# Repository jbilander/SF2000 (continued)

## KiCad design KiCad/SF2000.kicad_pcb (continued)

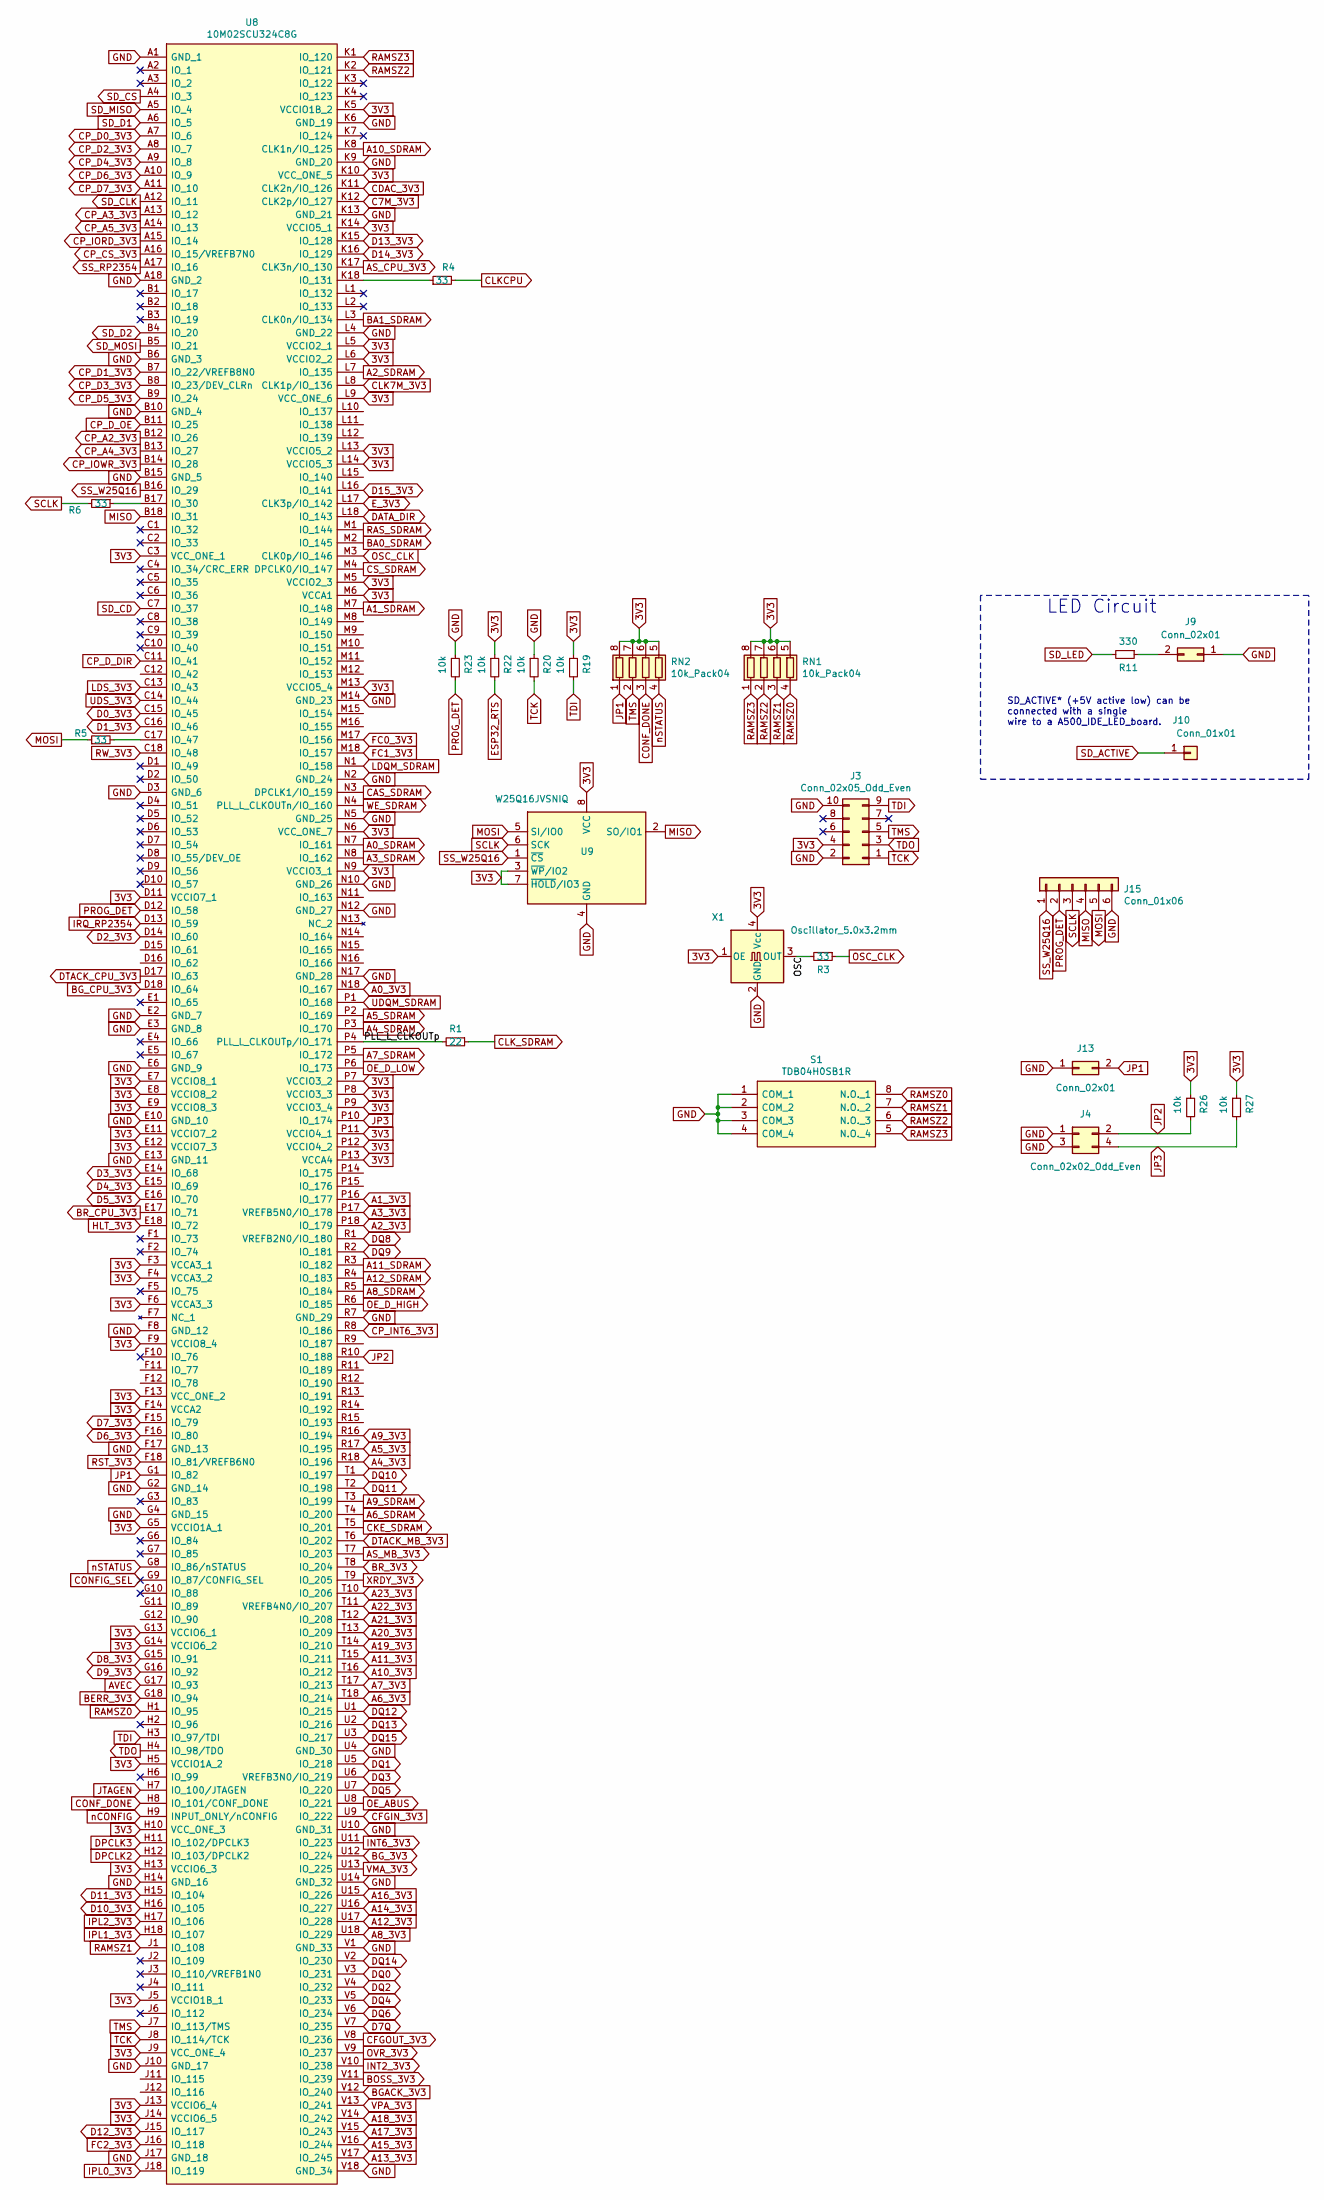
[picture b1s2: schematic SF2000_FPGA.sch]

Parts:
J3: Conn_02x05_Odd_Even; PinHeader_2x05_P2.54mm_Vertical
J4: Conn_02x02_Odd_Even; PinHeader_2x02_P2.54mm_Vertical
J9, J13: Conn_02x01; PinHeader_2x01_P2.54mm_Vertical
J10: Conn_01x01; PinHeader_1x01_P2.54mm_Horizontal
J15: Conn_01x06; PinHeader_1x06_P2.54mm_Vertical
R1: 22; R_0603_1608Metric_Pad0.98x0.95mm_HandSolder
R3, R4, R5, R6: 33; R_0603_1608Metric_Pad0.98x0.95mm_HandSolder
R11: 330; R_0603_1608Metric_Pad0.98x0.95mm_HandSolder
R19, R20, R22, R23, R26, R27: 10k; R_0603_1608Metric_Pad0.98x0.95mm_HandSolder
RN1, RN2: 10k_Pack04; RESCAF80P320X160X60-8N
S1: TDB04H0SB1R; TDB04H0SB1
U8: 10M02SCU324C8G; BGA-324_15.0x15.0mm_Layout18x18_P0.8mm_Ball0.5mm_Pad0.4mm_N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
U9: W25Q16JVSNIQ; SOIC-8_3.9x4.9mm_P1.27mm
X1: Oscillator_5.0x3.2mm; Oscillator_SMD_SeikoEpson_SG8002LB-4Pin_5.0x3.2mm

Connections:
3V3: J3.4, R19.1, R22.1, R26.1, R27.1, RN1.5 (R4.2), RN1.6 (R3.2), RN1.7 (R2.2), RN1.8 (R1.2), RN2.5 (R4.2), RN2.6 (R3.2), RN2.7 (R2.2), RN2.8 (R1.2), U8.C3 (VCC_ONE_1), U8.D11 (VCCIO7_1), U8.E7 (VCCIO8_1), U8.E8 (VCCIO8_2), U8.E9 (VCCIO8_3), U8.E11 (VCCIO7_2), U8.E12 (VCCIO7_3), U8.F3 (VCCA3_1), U8.F4 (VCCA3_2), U8.F6 (VCCA3_3), U8.F9 (VCCIO8_4), U8.F13 (VCC_ONE_2), U8.F14 (VCCA2), U8.G5 (VCCIO1A_1), U8.G13 (VCCIO6_1), U8.G14 (VCCIO6_2), U8.H5 (VCCIO1A_2), U8.H10 (VCC_ONE_3), U8.H13 (VCCIO6_3), U8.J5 (VCCIO1B_1), U8.J9 (VCC_ONE_4), U8.J13 (VCCIO6_4), U8.J14 (VCCIO6_5), U8.K5 (VCCIO1B_2), U8.K10 (VCC_ONE_5), U8.K14 (VCCIO5_1), U8.L5 (VCCIO2_1), U8.L6 (VCCIO2_2), U8.L9 (VCC_ONE_6), U8.L13 (VCCIO5_2), U8.L14 (VCCIO5_3), U8.M5 (VCCIO2_3), U8.M6 (VCCA1), U8.M13 (VCCIO5_4), U8.N6 (VCC_ONE_7), U8.N9 (VCCIO3_1), U8.P7 (VCCIO3_2), U8.P8 (VCCIO3_3), U8.P9 (VCCIO3_4), U8.P11 (VCCIO4_1), U8.P12 (VCCIO4_2), U8.P13 (VCCA4), U9.3 (~WP~/IO2), U9.7 (~HOLD~/IO3), U9.8 (VCC), X1.1 (OE), X1.4 (Vcc); also elsewhere on the board
/SF2000_FPGA/OSC: R3.2, X1.3 (OUT)
/SF2000_FPGA/PLL_L_CLKOUTp: R1.2, U8.P4 (PLL_L_CLKOUTp/IO_171)
A0_3V3: U8.N18 (IO_167); also elsewhere on the board
A0_SDRAM: U8.N7 (IO_161); also elsewhere on the board
A1_3V3: U8.P16 (IO_177); also elsewhere on the board
A1_SDRAM: U8.M7 (IO_148); also elsewhere on the board
A2_3V3: U8.P18 (IO_179); also elsewhere on the board
A2_SDRAM: U8.L7 (IO_135); also elsewhere on the board
A3_3V3: U8.P17 (VREFB5N0/IO_178); also elsewhere on the board
A3_SDRAM: U8.N8 (IO_162); also elsewhere on the board
A4_3V3: U8.R18 (IO_196); also elsewhere on the board
A4_SDRAM: U8.P3 (IO_170); also elsewhere on the board
A5_3V3: U8.R17 (IO_195); also elsewhere on the board
A5_SDRAM: U8.P2 (IO_169); also elsewhere on the board
A6_3V3: U8.T18 (IO_214); also elsewhere on the board
A6_SDRAM: U8.T4 (IO_200); also elsewhere on the board
A7_3V3: U8.T17 (IO_213); also elsewhere on the board
A7_SDRAM: U8.P5 (IO_172); also elsewhere on the board
A8_3V3: U8.U18 (IO_229); also elsewhere on the board
A8_SDRAM: U8.R5 (IO_184); also elsewhere on the board
A9_3V3: U8.R16 (IO_194); also elsewhere on the board
A9_SDRAM: U8.T3 (IO_199); also elsewhere on the board
A10_3V3: U8.T16 (IO_212); also elsewhere on the board
A10_SDRAM: U8.K8 (CLK1n/IO_125); also elsewhere on the board
A11_3V3: U8.T15 (IO_211); also elsewhere on the board
A11_SDRAM: U8.R3 (IO_182); also elsewhere on the board
A12_3V3: U8.U17 (IO_228); also elsewhere on the board
A12_SDRAM: U8.R4 (IO_183); also elsewhere on the board
A13_3V3: U8.V17 (IO_245); also elsewhere on the board
A14_3V3: U8.U16 (IO_227); also elsewhere on the board
A15_3V3: U8.V16 (IO_244); also elsewhere on the board
A16_3V3: U8.U15 (IO_226); also elsewhere on the board
A17_3V3: U8.V15 (IO_243); also elsewhere on the board
A18_3V3: U8.V14 (IO_242); also elsewhere on the board
A19_3V3: U8.T14 (IO_210); also elsewhere on the board
A20_3V3: U8.T13 (IO_209); also elsewhere on the board
A21_3V3: U8.T12 (IO_208); also elsewhere on the board
A22_3V3: U8.T11 (VREFB4N0/IO_207); also elsewhere on the board
A23_3V3: U8.T10 (IO_206); also elsewhere on the board
AS_CPU_3V3: U8.K17 (CLK3n/IO_130); also elsewhere on the board
AS_MB_3V3: U8.T7 (IO_203); also elsewhere on the board
AVEC: U8.G17 (IO_93); also elsewhere on the board
BA0_SDRAM: U8.M2 (IO_145); also elsewhere on the board
BA1_SDRAM: U8.L3 (CLK0n/IO_134); also elsewhere on the board
BERR_3V3: U8.G18 (IO_94); also elsewhere on the board
BGACK_3V3: U8.V12 (IO_240); also elsewhere on the board
BG_3V3: U8.U12 (IO_224); also elsewhere on the board
BG_CPU_3V3: U8.D18 (IO_64); also elsewhere on the board
BOSS_3V3: U8.V11 (IO_239); also elsewhere on the board
BR_3V3: U8.T8 (IO_204); also elsewhere on the board
BR_CPU_3V3: U8.E17 (IO_71); also elsewhere on the board
C7M_3V3: U8.K12 (CLK2p/IO_127); also elsewhere on the board
CAS_SDRAM: U8.N3 (DPCLK1/IO_159); also elsewhere on the board
CDAC_3V3: U8.K11 (CLK2n/IO_126); also elsewhere on the board
CFGIN_3V3: U8.U9 (IO_222); also elsewhere on the board
CFGOUT_3V3: U8.V8 (IO_236); also elsewhere on the board
CKE_SDRAM: U8.T5 (IO_201); also elsewhere on the board
CLK7M_3V3: U8.L8 (CLK1p/IO_136); also elsewhere on the board
CLKCPU: R4.2; also elsewhere on the board
CLK_SDRAM: R1.1; also elsewhere on the board
CONFIG_SEL: U8.G9 (IO_87/CONFIG_SEL)
CONF_DONE: RN2.3 (R3.1), U8.H8 (IO_101/CONF_DONE)
CP_A2_3V3: U8.B12 (IO_26); also elsewhere on the board
CP_A3_3V3: U8.A13 (IO_12); also elsewhere on the board
CP_A4_3V3: U8.B13 (IO_27); also elsewhere on the board
CP_A5_3V3: U8.A14 (IO_13); also elsewhere on the board
CP_CS_3V3: U8.A16 (IO_15/VREFB7N0); also elsewhere on the board
CP_D0_3V3: U8.A7 (IO_6); also elsewhere on the board
CP_D1_3V3: U8.B7 (IO_22/VREFB8N0); also elsewhere on the board
CP_D2_3V3: U8.A8 (IO_7); also elsewhere on the board
CP_D3_3V3: U8.B8 (IO_23/DEV_CLRn); also elsewhere on the board
CP_D4_3V3: U8.A9 (IO_8); also elsewhere on the board
CP_D5_3V3: U8.B9 (IO_24); also elsewhere on the board
CP_D6_3V3: U8.A10 (IO_9); also elsewhere on the board
CP_D7_3V3: U8.A11 (IO_10); also elsewhere on the board
CP_D_DIR: U8.C11 (IO_41); also elsewhere on the board
CP_D_OE: U8.B11 (IO_25); also elsewhere on the board
CP_INT6_3V3: U8.R8 (IO_186); also elsewhere on the board
CP_IORD_3V3: U8.A15 (IO_14); also elsewhere on the board
CP_IOWR_3V3: U8.B14 (IO_28); also elsewhere on the board
CS_SDRAM: U8.M4 (DPCLK0/IO_147); also elsewhere on the board
D0_3V3: U8.C15 (IO_45); also elsewhere on the board
D1_3V3: U8.C16 (IO_46); also elsewhere on the board
D2_3V3: U8.D14 (IO_60); also elsewhere on the board
D3_3V3: U8.E14 (IO_68); also elsewhere on the board
D4_3V3: U8.E15 (IO_69); also elsewhere on the board
D5_3V3: U8.E16 (IO_70); also elsewhere on the board
D6_3V3: U8.F16 (IO_80); also elsewhere on the board
D7Q: U8.V7 (IO_235); also elsewhere on the board
D7_3V3: U8.F15 (IO_79); also elsewhere on the board
D8_3V3: U8.G15 (IO_91); also elsewhere on the board
D9_3V3: U8.G16 (IO_92); also elsewhere on the board
D10_3V3: U8.H16 (IO_105); also elsewhere on the board
D11_3V3: U8.H15 (IO_104); also elsewhere on the board
D12_3V3: U8.J15 (IO_117); also elsewhere on the board
D13_3V3: U8.K15 (IO_128); also elsewhere on the board
D14_3V3: U8.K16 (IO_129); also elsewhere on the board
D15_3V3: U8.L16 (IO_141); also elsewhere on the board
DATA_DIR: U8.L18 (IO_143); also elsewhere on the board
DPCLK2: U8.H12 (IO_103/DPCLK2)
DPCLK3: U8.H11 (IO_102/DPCLK3)
DQ0: U8.V3 (IO_231); also elsewhere on the board
DQ1: U8.U5 (IO_218); also elsewhere on the board
DQ2: U8.V4 (IO_232); also elsewhere on the board
DQ3: U8.U6 (VREFB3N0/IO_219); also elsewhere on the board
DQ4: U8.V5 (IO_233); also elsewhere on the board
DQ5: U8.U7 (IO_220); also elsewhere on the board
DQ6: U8.V6 (IO_234); also elsewhere on the board
DQ8: U8.R1 (VREFB2N0/IO_180); also elsewhere on the board
DQ9: U8.R2 (IO_181); also elsewhere on the board
DQ10: U8.T1 (IO_197); also elsewhere on the board
DQ11: U8.T2 (IO_198); also elsewhere on the board
DQ12: U8.U1 (IO_215); also elsewhere on the board
DQ13: U8.U2 (IO_216); also elsewhere on the board
DQ14: U8.V2 (IO_230); also elsewhere on the board
DQ15: U8.U3 (IO_217); also elsewhere on the board
DTACK_CPU_3V3: U8.D17 (IO_63); also elsewhere on the board
DTACK_MB_3V3: U8.T6 (IO_202); also elsewhere on the board
ESP32_RTS: R22.2; also elsewhere on the board
E_3V3: U8.L17 (CLK3p/IO_142); also elsewhere on the board
FC0_3V3: U8.M17 (IO_156); also elsewhere on the board
FC1_3V3: U8.M18 (IO_157); also elsewhere on the board
FC2_3V3: U8.J16 (IO_118); also elsewhere on the board
GND: J3.2, J3.10, J4.1, J4.3, J9.1, J13.1, J15.6, R20.1, R23.1, S1.1 (COM_1), S1.2 (COM_2), S1.3 (COM_3), S1.4 (COM_4), U8.A1 (GND_1), U8.A18 (GND_2), U8.B6 (GND_3), U8.B10 (GND_4), U8.B15 (GND_5), U8.D3 (GND_6), U8.E2 (GND_7), U8.E3 (GND_8), U8.E6 (GND_9), U8.E10 (GND_10), U8.E13 (GND_11), U8.F8 (GND_12), U8.F17 (GND_13), U8.G2 (GND_14), U8.G4 (GND_15), U8.H14 (GND_16), U8.J10 (GND_17), U8.J17 (GND_18), U8.K6 (GND_19), U8.K9 (GND_20), U8.K13 (GND_21), U8.L4 (GND_22), U8.M14 (GND_23), U8.N2 (GND_24), U8.N5 (GND_25), U8.N10 (GND_26), U8.N12 (GND_27), U8.N17 (GND_28), U8.R7 (GND_29), U8.U4 (GND_30), U8.U10 (GND_31), U8.U14 (GND_32), U8.V1 (GND_33), U8.V18 (GND_34), U9.4 (GND), X1.2 (GND); also elsewhere on the board
HLT_3V3: U8.E18 (IO_72); also elsewhere on the board
INT2_3V3: U8.V10 (IO_238); also elsewhere on the board
INT6_3V3: U8.U11 (IO_223); also elsewhere on the board
IPL0_3V3: U8.J18 (IO_119); also elsewhere on the board
IPL1_3V3: U8.H18 (IO_107); also elsewhere on the board
IPL2_3V3: U8.H17 (IO_106); also elsewhere on the board
IRQ_RP2354: U8.D13 (IO_59); also elsewhere on the board
JP1: J13.2, RN2.1 (R1.1), U8.G1 (IO_82)
JP2: J4.2, R26.2, U8.R10 (IO_188)
JP3: J4.4, R27.2, U8.P10 (IO_174)
JTAGEN: U8.H7 (IO_100/JTAGEN)
LDQM_SDRAM: U8.N1 (IO_158); also elsewhere on the board
LDS_3V3: U8.C13 (IO_43); also elsewhere on the board
MISO: J15.4, U8.B18 (IO_31), U9.2 (SO/IO1); also elsewhere on the board
MOSI: J15.5, R5.1, U9.5 (SI/IO0); also elsewhere on the board
unnamed: J9.2, R11.1
unnamed: R4.1, U8.K18 (IO_131)
unnamed: R5.2, U8.C17 (IO_47)
unnamed: R6.1, U8.B17 (IO_30)
OE_ABUS: U8.U8 (IO_221); also elsewhere on the board
OE_D_HIGH: U8.R6 (IO_185); also elsewhere on the board
OE_D_LOW: U8.P6 (IO_173); also elsewhere on the board
OSC_CLK: R3.1, U8.M3 (CLK0p/IO_146)
OVR_3V3: U8.V9 (IO_237); also elsewhere on the board
PROG_DET: J15.2, R23.2, U8.D12 (IO_58)
RAMSZ0: RN1.4 (R4.1), S1.8 (N.O._1), U8.H1 (IO_95)
RAMSZ1: RN1.3 (R3.1), S1.7 (N.O._2), U8.J1 (IO_108)
RAMSZ2: RN1.2 (R2.1), S1.6 (N.O._3), U8.K2 (IO_121)
RAMSZ3: RN1.1 (R1.1), S1.5 (N.O._4), U8.K1 (IO_120)
RAS_SDRAM: U8.M1 (IO_144); also elsewhere on the board
RST_3V3: U8.F18 (IO_81/VREFB6N0); also elsewhere on the board
RW_3V3: U8.C18 (IO_48); also elsewhere on the board
SCLK: J15.3, R6.2, U9.6 (SCK); also elsewhere on the board
SD_ACTIVE: J10.1; also elsewhere on the board
SD_CD: U8.C7 (IO_37); also elsewhere on the board
SD_CLK: U8.A12 (IO_11); also elsewhere on the board
SD_CS: U8.A4 (IO_3); also elsewhere on the board
SD_D1: U8.A6 (IO_5); also elsewhere on the board
SD_D2: U8.B4 (IO_20); also elsewhere on the board
SD_LED: R11.2; also elsewhere on the board
SD_MISO: U8.A5 (IO_4); also elsewhere on the board
SD_MOSI: U8.B5 (IO_21); also elsewhere on the board
SS_RP2354: U8.A17 (IO_16); also elsewhere on the board
SS_W25Q16: J15.1, U8.B16 (IO_29), U9.1 (~CS); also elsewhere on the board
TCK: J3.1, R20.2, U8.J8 (IO_114/TCK)
TDI: J3.9, R19.2, U8.H3 (IO_97/TDI)
TDO: J3.3, U8.H4 (IO_98/TDO)
TMS: J3.5, RN2.2 (R2.1), U8.J7 (IO_113/TMS)
UDQM_SDRAM: U8.P1 (IO_168); also elsewhere on the board
UDS_3V3: U8.C14 (IO_44); also elsewhere on the board
VMA_3V3: U8.U13 (IO_225); also elsewhere on the board
VPA_3V3: U8.V13 (IO_241); also elsewhere on the board
WE_SDRAM: U8.N4 (PLL_L_CLKOUTn/IO_160); also elsewhere on the board
XRDY_3V3: U8.T9 (IO_205); also elsewhere on the board
nCONFIG: U8.H9 (INPUT_ONLY/nCONFIG); also elsewhere on the board
nSTATUS: RN2.4 (R4.1), U8.G8 (IO_86/nSTATUS)

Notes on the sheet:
LED Circuit
SD_ACTIVE* (+5V active low) can be connected with a single wire to a A500_IDE_LED_board.

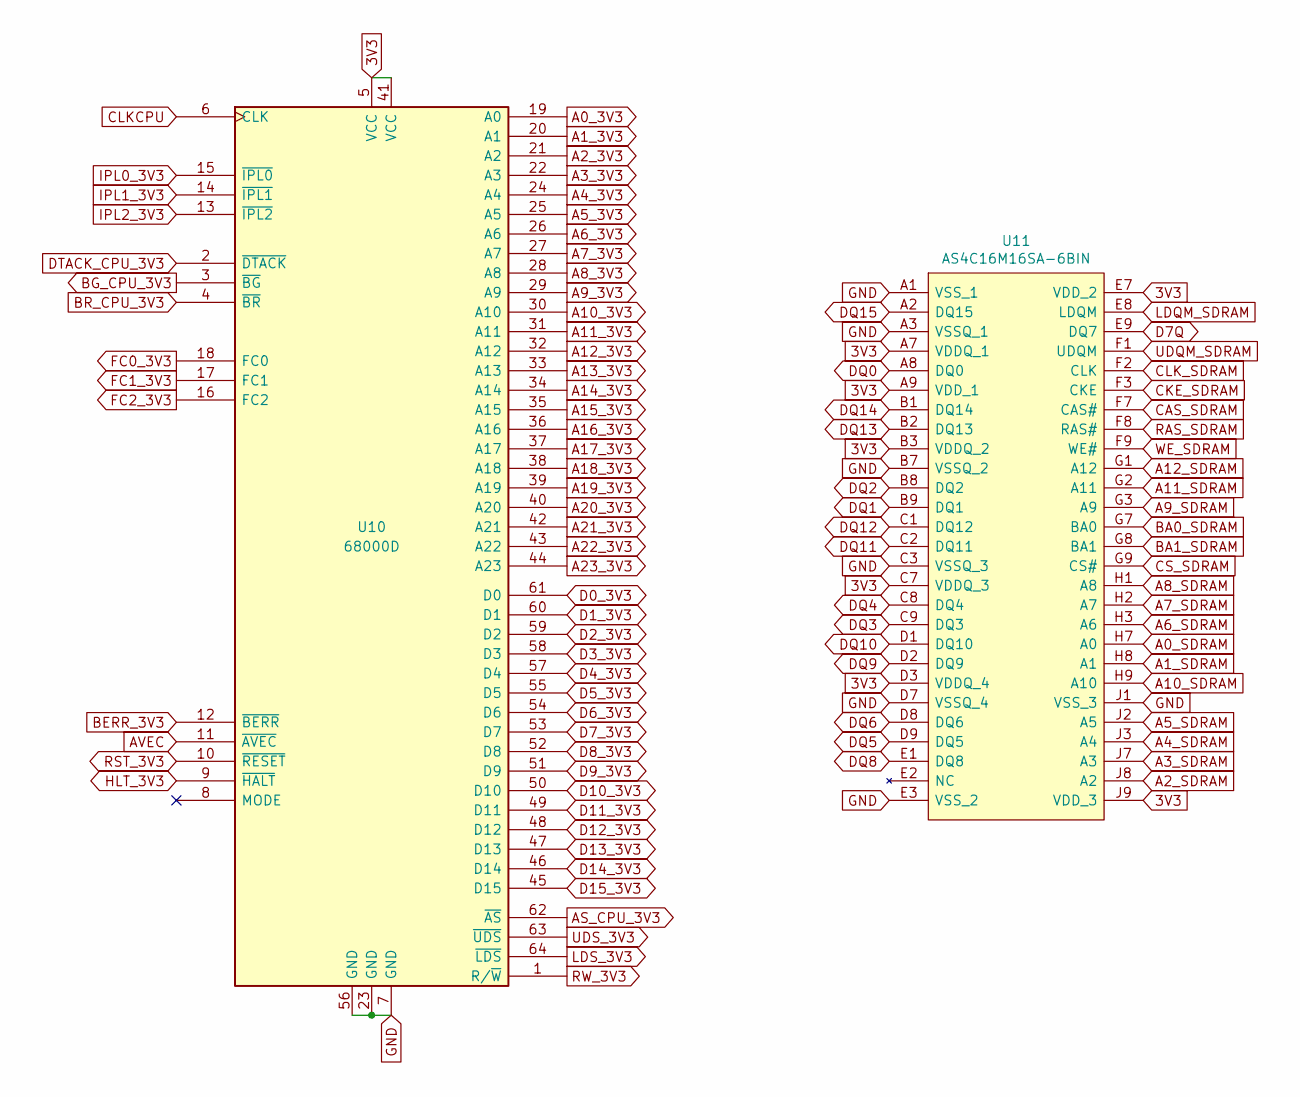
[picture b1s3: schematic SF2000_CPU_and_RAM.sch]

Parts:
U10: 68000D; QFP-64_14x14mm_Pitch0.8mm
U11: AS4C16M16SA-6BIN; BGA54C80P9X9_800X800X120

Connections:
3V3: U10.5 (VCC), U10.41 (VCC), U11.A7 (VDDQ_1), U11.A9 (VDD_1), U11.B3 (VDDQ_2), U11.C7 (VDDQ_3), U11.D3 (VDDQ_4), U11.E7 (VDD_2), U11.J9 (VDD_3); also elsewhere on the board
A0_3V3: U10.19 (A0); also elsewhere on the board
A0_SDRAM: U11.H7 (A0); also elsewhere on the board
A1_3V3: U10.20 (A1); also elsewhere on the board
A1_SDRAM: U11.H8 (A1); also elsewhere on the board
A2_3V3: U10.21 (A2); also elsewhere on the board
A2_SDRAM: U11.J8 (A2); also elsewhere on the board
A3_3V3: U10.22 (A3); also elsewhere on the board
A3_SDRAM: U11.J7 (A3); also elsewhere on the board
A4_3V3: U10.24 (A4); also elsewhere on the board
A4_SDRAM: U11.J3 (A4); also elsewhere on the board
A5_3V3: U10.25 (A5); also elsewhere on the board
A5_SDRAM: U11.J2 (A5); also elsewhere on the board
A6_3V3: U10.26 (A6); also elsewhere on the board
A6_SDRAM: U11.H3 (A6); also elsewhere on the board
A7_3V3: U10.27 (A7); also elsewhere on the board
A7_SDRAM: U11.H2 (A7); also elsewhere on the board
A8_3V3: U10.28 (A8); also elsewhere on the board
A8_SDRAM: U11.H1 (A8); also elsewhere on the board
A9_3V3: U10.29 (A9); also elsewhere on the board
A9_SDRAM: U11.G3 (A9); also elsewhere on the board
A10_3V3: U10.30 (A10); also elsewhere on the board
A10_SDRAM: U11.H9 (A10); also elsewhere on the board
A11_3V3: U10.31 (A11); also elsewhere on the board
A11_SDRAM: U11.G2 (A11); also elsewhere on the board
A12_3V3: U10.32 (A12); also elsewhere on the board
A12_SDRAM: U11.G1 (A12); also elsewhere on the board
A13_3V3: U10.33 (A13); also elsewhere on the board
A14_3V3: U10.34 (A14); also elsewhere on the board
A15_3V3: U10.35 (A15); also elsewhere on the board
A16_3V3: U10.36 (A16); also elsewhere on the board
A17_3V3: U10.37 (A17); also elsewhere on the board
A18_3V3: U10.38 (A18); also elsewhere on the board
A19_3V3: U10.39 (A19); also elsewhere on the board
A20_3V3: U10.40 (A20); also elsewhere on the board
A21_3V3: U10.42 (A21); also elsewhere on the board
A22_3V3: U10.43 (A22); also elsewhere on the board
A23_3V3: U10.44 (A23); also elsewhere on the board
AS_CPU_3V3: U10.62 (~AS); also elsewhere on the board
AVEC: U10.11 (~AVEC); also elsewhere on the board
BA0_SDRAM: U11.G7 (BA0); also elsewhere on the board
BA1_SDRAM: U11.G8 (BA1); also elsewhere on the board
BERR_3V3: U10.12 (~BERR); also elsewhere on the board
BG_CPU_3V3: U10.3 (~BG); also elsewhere on the board
BR_CPU_3V3: U10.4 (~BR); also elsewhere on the board
CAS_SDRAM: U11.F7 (CAS#); also elsewhere on the board
CKE_SDRAM: U11.F3 (CKE); also elsewhere on the board
CLKCPU: U10.6 (CLK); also elsewhere on the board
CLK_SDRAM: U11.F2 (CLK); also elsewhere on the board
CS_SDRAM: U11.G9 (CS#); also elsewhere on the board
D0_3V3: U10.61 (D0); also elsewhere on the board
D1_3V3: U10.60 (D1); also elsewhere on the board
D2_3V3: U10.59 (D2); also elsewhere on the board
D3_3V3: U10.58 (D3); also elsewhere on the board
D4_3V3: U10.57 (D4); also elsewhere on the board
D5_3V3: U10.55 (D5); also elsewhere on the board
D6_3V3: U10.54 (D6); also elsewhere on the board
D7Q: U11.E9 (DQ7); also elsewhere on the board
D7_3V3: U10.53 (D7); also elsewhere on the board
D8_3V3: U10.52 (D8); also elsewhere on the board
D9_3V3: U10.51 (D9); also elsewhere on the board
D10_3V3: U10.50 (D10); also elsewhere on the board
D11_3V3: U10.49 (D11); also elsewhere on the board
D12_3V3: U10.48 (D12); also elsewhere on the board
D13_3V3: U10.47 (D13); also elsewhere on the board
D14_3V3: U10.46 (D14); also elsewhere on the board
D15_3V3: U10.45 (D15); also elsewhere on the board
DQ0: U11.A8 (DQ0); also elsewhere on the board
DQ1: U11.B9 (DQ1); also elsewhere on the board
DQ2: U11.B8 (DQ2); also elsewhere on the board
DQ3: U11.C9 (DQ3); also elsewhere on the board
DQ4: U11.C8 (DQ4); also elsewhere on the board
DQ5: U11.D9 (DQ5); also elsewhere on the board
DQ6: U11.D8 (DQ6); also elsewhere on the board
DQ8: U11.E1 (DQ8); also elsewhere on the board
DQ9: U11.D2 (DQ9); also elsewhere on the board
DQ10: U11.D1 (DQ10); also elsewhere on the board
DQ11: U11.C2 (DQ11); also elsewhere on the board
DQ12: U11.C1 (DQ12); also elsewhere on the board
DQ13: U11.B2 (DQ13); also elsewhere on the board
DQ14: U11.B1 (DQ14); also elsewhere on the board
DQ15: U11.A2 (DQ15); also elsewhere on the board
DTACK_CPU_3V3: U10.2 (~DTACK); also elsewhere on the board
FC0_3V3: U10.18 (FC0); also elsewhere on the board
FC1_3V3: U10.17 (FC1); also elsewhere on the board
FC2_3V3: U10.16 (FC2); also elsewhere on the board
GND: U10.7 (GND), U10.23 (GND), U10.56 (GND), U11.A1 (VSS_1), U11.A3 (VSSQ_1), U11.B7 (VSSQ_2), U11.C3 (VSSQ_3), U11.D7 (VSSQ_4), U11.E3 (VSS_2), U11.J1 (VSS_3); also elsewhere on the board
HLT_3V3: U10.9 (~HALT); also elsewhere on the board
IPL0_3V3: U10.15 (~IPL0); also elsewhere on the board
IPL1_3V3: U10.14 (~IPL1); also elsewhere on the board
IPL2_3V3: U10.13 (~IPL2); also elsewhere on the board
LDQM_SDRAM: U11.E8 (LDQM); also elsewhere on the board
LDS_3V3: U10.64 (~LDS); also elsewhere on the board
RAS_SDRAM: U11.F8 (RAS#); also elsewhere on the board
RST_3V3: U10.10 (~RESET); also elsewhere on the board
RW_3V3: U10.1 (R/~W); also elsewhere on the board
UDQM_SDRAM: U11.F1 (UDQM); also elsewhere on the board
UDS_3V3: U10.63 (~UDS); also elsewhere on the board
WE_SDRAM: U11.F9 (WE#); also elsewhere on the board

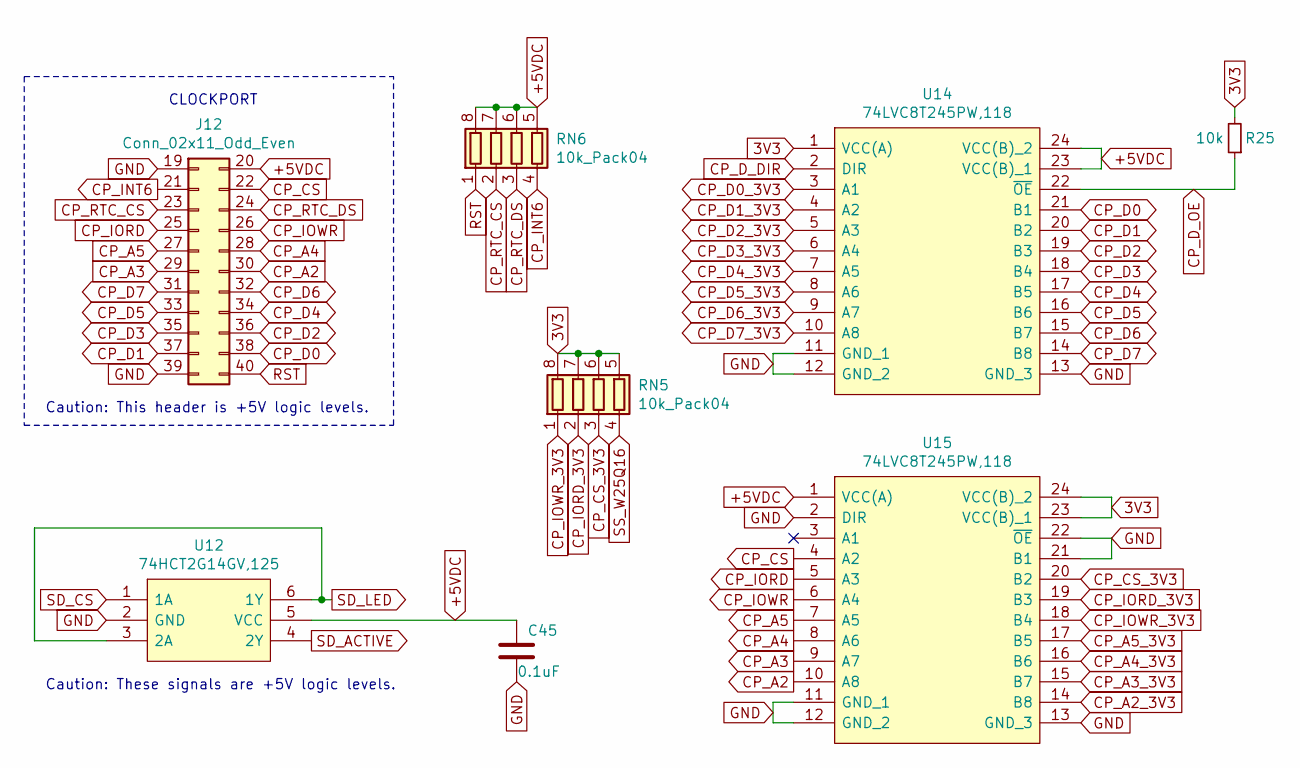
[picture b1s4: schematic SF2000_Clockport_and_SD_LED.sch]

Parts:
C45: 0.1uF; C_0603_1608Metric_Pad1.08x0.95mm_HandSolder
J12: Conn_02x11_Odd_Even; PinHeader_2x11_P2.00mm_Vertical
R25: 10k; R_0603_1608Metric_Pad0.98x0.95mm_HandSolder
RN5, RN6: 10k_Pack04; RESCAF80P320X160X60-8N
U12: 74HCT2G14GV,125; TSOP-6_1.65x3.05mm_P0.95mm
U14, U15: 74LVC8T245PW,118; TSSOP-24_4.4x7.8mm_P0.65mm

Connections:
3V3: R25.2, RN5.5 (R4.2), RN5.6 (R3.2), RN5.7 (R2.2), RN5.8 (R1.2), U14.1 (VCC(A)), U15.23 (VCC(B)_1), U15.24 (VCC(B)_2); also elsewhere on the board
+5VDC: C45.1, J12.20, RN6.5 (R4.2), RN6.6 (R3.2), RN6.7 (R2.2), RN6.8 (R1.2), U12.5 (VCC), U14.23 (VCC(B)_1), U14.24 (VCC(B)_2), U15.1 (VCC(A)); also elsewhere on the board
CP_A2: J12.30, U15.10 (A8)
CP_A2_3V3: U15.14 (B8); also elsewhere on the board
CP_A3: J12.29, U15.9 (A7)
CP_A3_3V3: U15.15 (B7); also elsewhere on the board
CP_A4: J12.28, U15.8 (A6)
CP_A4_3V3: U15.16 (B6); also elsewhere on the board
CP_A5: J12.27, U15.7 (A5)
CP_A5_3V3: U15.17 (B5); also elsewhere on the board
CP_CS: J12.22, U15.4 (A2)
CP_CS_3V3: RN5.3 (R3.1), U15.20 (B2); also elsewhere on the board
CP_D0: J12.38, U14.21 (B1)
CP_D0_3V3: U14.3 (A1); also elsewhere on the board
CP_D1: J12.37, U14.20 (B2)
CP_D1_3V3: U14.4 (A2); also elsewhere on the board
CP_D2: J12.36, U14.19 (B3)
CP_D2_3V3: U14.5 (A3); also elsewhere on the board
CP_D3: J12.35, U14.18 (B4)
CP_D3_3V3: U14.6 (A4); also elsewhere on the board
CP_D4: J12.34, U14.17 (B5)
CP_D4_3V3: U14.7 (A5); also elsewhere on the board
CP_D5: J12.33, U14.16 (B6)
CP_D5_3V3: U14.8 (A6); also elsewhere on the board
CP_D6: J12.32, U14.15 (B7)
CP_D6_3V3: U14.9 (A7); also elsewhere on the board
CP_D7: J12.31, U14.14 (B8)
CP_D7_3V3: U14.10 (A8); also elsewhere on the board
CP_D_DIR: U14.2 (DIR); also elsewhere on the board
CP_D_OE: R25.1, U14.22 (~OE); also elsewhere on the board
CP_INT6: J12.21, RN6.4 (R4.1); also elsewhere on the board
CP_IORD: J12.25, U15.5 (A3)
CP_IORD_3V3: RN5.2 (R2.1), U15.19 (B3); also elsewhere on the board
CP_IOWR: J12.26, U15.6 (A4)
CP_IOWR_3V3: RN5.1 (R1.1), U15.18 (B4); also elsewhere on the board
CP_RTC_CS: J12.23, RN6.2 (R2.1)
CP_RTC_DS: J12.24, RN6.3 (R3.1)
GND: C45.2, J12.19, J12.39, U12.2 (GND), U14.11 (GND_1), U14.12 (GND_2), U14.13 (GND_3), U15.2 (DIR), U15.11 (GND_1), U15.12 (GND_2), U15.13 (GND_3), U15.21 (B1), U15.22 (~OE); also elsewhere on the board
RST: J12.40, RN6.1 (R1.1); also elsewhere on the board
SD_ACTIVE: U12.4 (2Y); also elsewhere on the board
SD_CS: U12.1 (1A); also elsewhere on the board
SD_LED: U12.3 (2A), U12.6 (1Y); also elsewhere on the board
SS_W25Q16: RN5.4 (R4.1); also elsewhere on the board

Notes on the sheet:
CLOCKPORT
Caution: This header is +5V logic levels.
Caution: These signals are +5V logic levels.

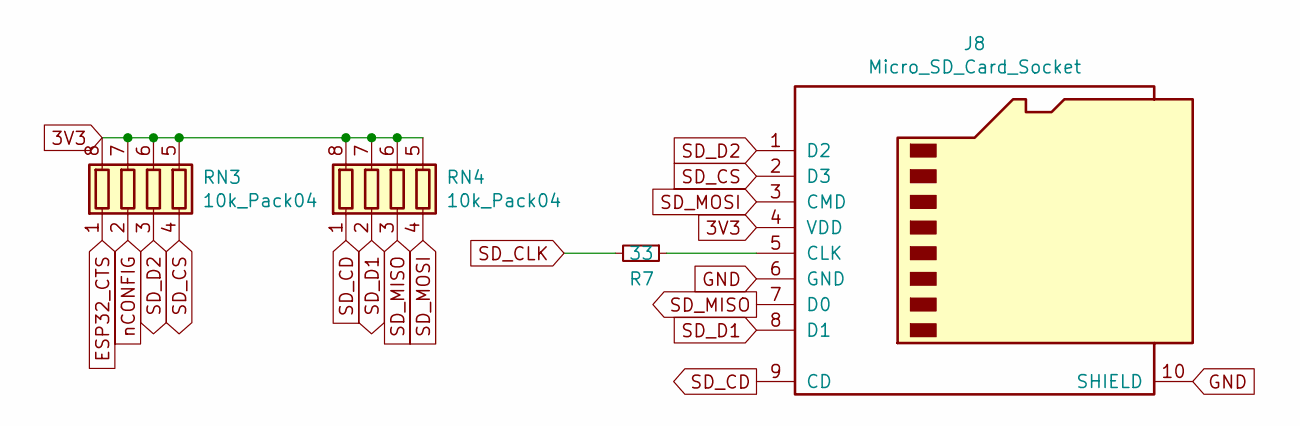
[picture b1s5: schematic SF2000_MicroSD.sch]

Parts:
J8: Micro_SD_Card_Socket; GCT-MEM2055-00-190-01-A
R7: 33; R_0603_1608Metric_Pad0.98x0.95mm_HandSolder
RN3, RN4: 10k_Pack04; RESCAF80P320X160X60-8N

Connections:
3V3: J8.4 (VDD), RN3.5 (R4.2), RN3.6 (R3.2), RN3.7 (R2.2), RN3.8 (R1.2), RN4.5 (R4.2), RN4.6 (R3.2), RN4.7 (R2.2), RN4.8 (R1.2); also elsewhere on the board
ESP32_CTS: RN3.1 (R1.1); also elsewhere on the board
GND: J8.6 (GND), J8.10 (SHIELD); also elsewhere on the board
unnamed: J8.5 (CLK), R7.1
SD_CD: J8.9 (CD), RN4.1 (R1.1); also elsewhere on the board
SD_CLK: R7.2; also elsewhere on the board
SD_CS: J8.2 (D3), RN3.4 (R4.1); also elsewhere on the board
SD_D1: J8.8 (D1), RN4.2 (R2.1); also elsewhere on the board
SD_D2: J8.1 (D2), RN3.3 (R3.1); also elsewhere on the board
SD_MISO: J8.7 (D0), RN4.3 (R3.1); also elsewhere on the board
SD_MOSI: J8.3 (CMD), RN4.4 (R4.1); also elsewhere on the board
nCONFIG: RN3.2 (R2.1); also elsewhere on the board

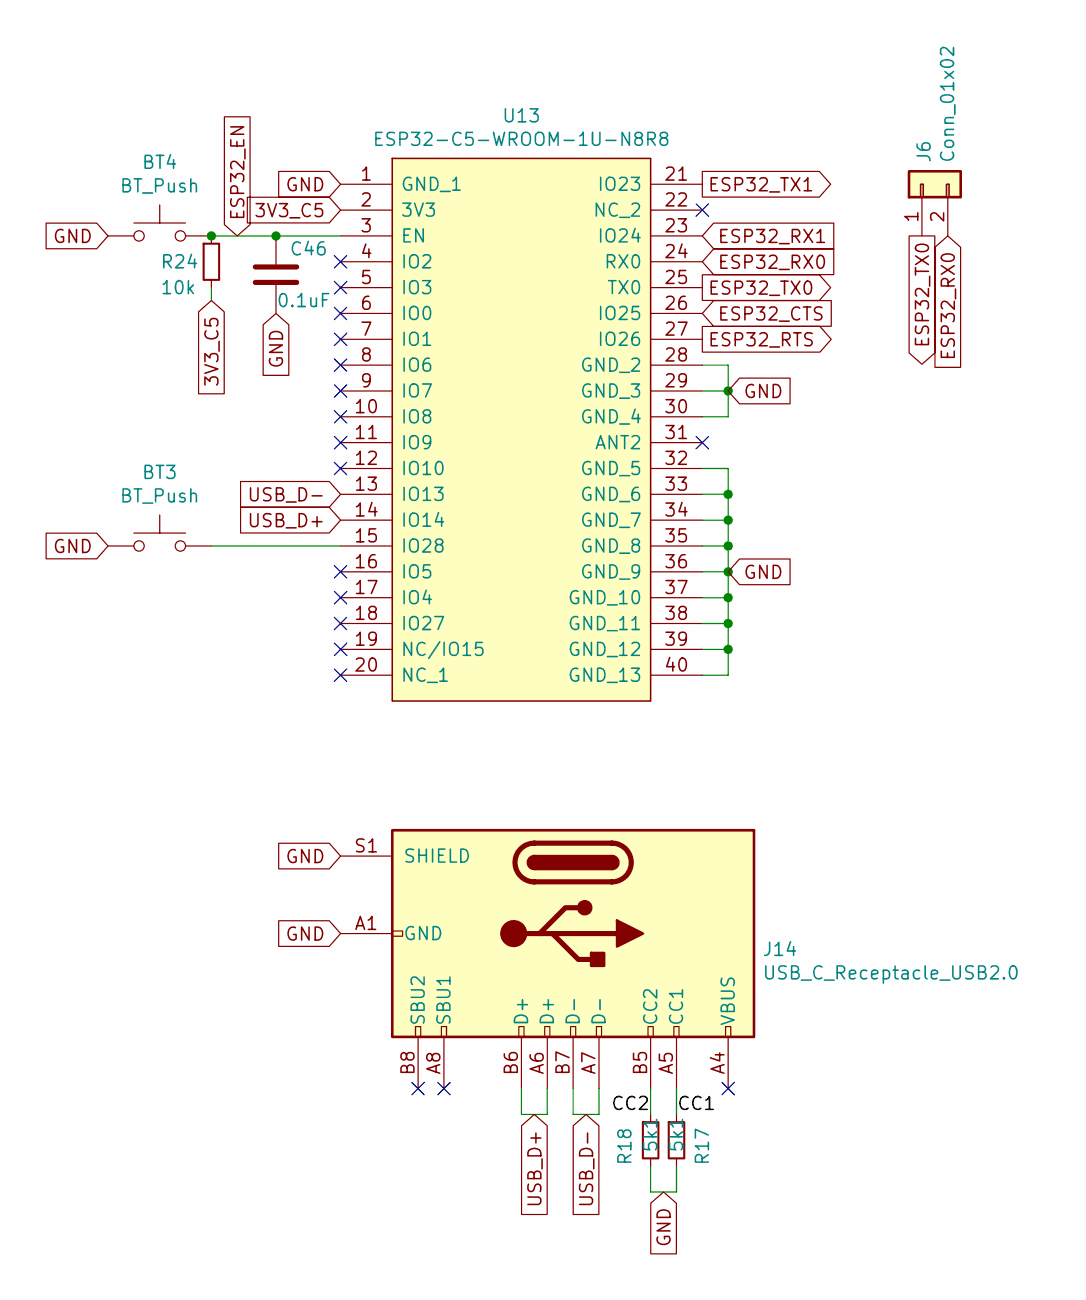
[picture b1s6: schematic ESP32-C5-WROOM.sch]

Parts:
BT3, BT4: BT_Push; Sunrom_Tactile_Switch_3x4x2mm_SMD_2-Pin
C46: 0.1uF; C_0603_1608Metric_Pad1.08x0.95mm_HandSolder
J6: Conn_01x02; PinHeader_1x02_P2.54mm_Vertical
J14: USB_C_Receptacle_USB2.0; USB_C_Receptacle_HRO_TYPE-C-31-M-12
R17, R18: 5k1; R_0603_1608Metric_Pad0.98x0.95mm_HandSolder
R24: 10k; R_0603_1608Metric_Pad0.98x0.95mm_HandSolder
U13: ESP32-C5-WROOM-1U-N8R8; ESP32C5WROOM1UN8R8

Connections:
3V3_C5: R24.2, U13.2 (3V3); also elsewhere on the board
/ESP32-C5-WROOM/CC1: J14.A5 (CC1), R17.1
/ESP32-C5-WROOM/CC2: J14.B5 (CC2), R18.1
ESP32_CTS: U13.26 (IO25); also elsewhere on the board
ESP32_EN: BT4.2, C46.1, R24.1, U13.3 (EN); also elsewhere on the board
ESP32_RTS: U13.27 (IO26); also elsewhere on the board
ESP32_RX0: J6.2, U13.24 (RX0)
ESP32_RX1: U13.23 (IO24); also elsewhere on the board
ESP32_TX0: J6.1, U13.25 (TX0)
ESP32_TX1: U13.21 (IO23); also elsewhere on the board
GND: BT3.1, BT4.1, C46.2, J14.A1 (GND), J14.A12 (GND), J14.B1 (GND), J14.B12 (GND), J14.S1 (SHIELD), R17.2, R18.2, U13.1 (GND_1), U13.28 (GND_2), U13.29 (GND_3), U13.30 (GND_4), U13.32 (GND_5), U13.33 (GND_6), U13.34 (GND_7), U13.35 (GND_8), U13.36 (GND_9), U13.37 (GND_10), U13.38 (GND_11), U13.39 (GND_12), U13.40 (GND_13); also elsewhere on the board
unnamed: BT3.2, U13.15 (IO28)
unnamed: J14.A4 (VBUS), J14.A9 (VBUS), J14.B4 (VBUS), J14.B9 (VBUS)
USB_D+: J14.A6 (D+), J14.B6 (D+), U13.14 (IO14)
USB_D−: J14.A7 (D-), J14.B7 (D-), U13.13 (IO13)
